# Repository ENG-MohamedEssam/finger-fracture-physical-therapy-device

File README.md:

# finger-fracture-physical-therapy-device

#### Note that this whole project was made by me from the Reverse-Engineering phase to the design to the fabrication of the final product

## **Abstract**

#### This project was for helping the physical therapist to help aid the patiets that had a broken or fractured finger
#### The device mainly uses a potentiometer to send the data of the the finger's angle to LCD and to the phone through a bluetooth module
#### The device has Arduino Nano as it's main controller, Potentiometer to send the Angle Data, LCD to show the data, Bluetooth module to send the data to the phone , 2 push buttons one for the hold of the readings, the second is for getting the angles in degree and minute format

#### The project went throgh four phases

## Phase 1 Idea
#### The idea was to replicate the behaviour of a digital protractor device that was already in the market to invent something that may help the patients with broken fingers
## Phase 2 Reverse-Engineering
#### So i started Reverse-Engineering the Digital protractor as shown below 

#### When i understood it's behaviour i started to find similar components in the Egyptian market 
#### the components that i didn't find was the induction encoder so i had to find a replacement
#### i thought of three things, Potentiometer, Normal Encoder, IMU
#### I even wrote codes for the three sesors.
## Problems 
#### IMU was too expensive for such a project but it kind of worked correctly
#### The encoders in Egypt had too little pulses so the error in Degrees was not acceptable
#### The potentiometer was the cheapest sensor so in mass production that was the ideal choice but it gave an error in the reading as well that was not acceptable and the Arduino Nano was only 10 bits in ADC

## Scenario to fix the Potentiameter's problem
#### To fix the problem in the potentiometer there were two solutions either i use the algorithm over sampling and decimation or i use the sliding window filter
#### so i went along with the over sampling and decimation technique, it was by having many readings in an array then get the average of it many times, that makes the reading more accurate.
#### The error after that algorithm was +/- 0.02 and that was more than acceptable.

## Phase 3 Design
#### In this phase i started to design the circuit on protues such as follows

#### After i made sure it works fine i turned to try the components connections on a bread board as follows 

#### Then i designed the circuit on Eagle-Cad program 
#### I even designed one of the three parts on SolidWorks as you can see below 

#### the other two parts were open source 

## Phase 4 fabrication
#### in this phase i fabricated the PCB and tested it and it worked fine, below are some images of the final product (The band)
.jpeg)

#### The following is a video of me explaining how the whole process works
[Explanation](https://drive.google.com/drive/folders/1u0ruocD8NN2b_IU45vWWJVkj_FHNx0_M?usp=share_link)

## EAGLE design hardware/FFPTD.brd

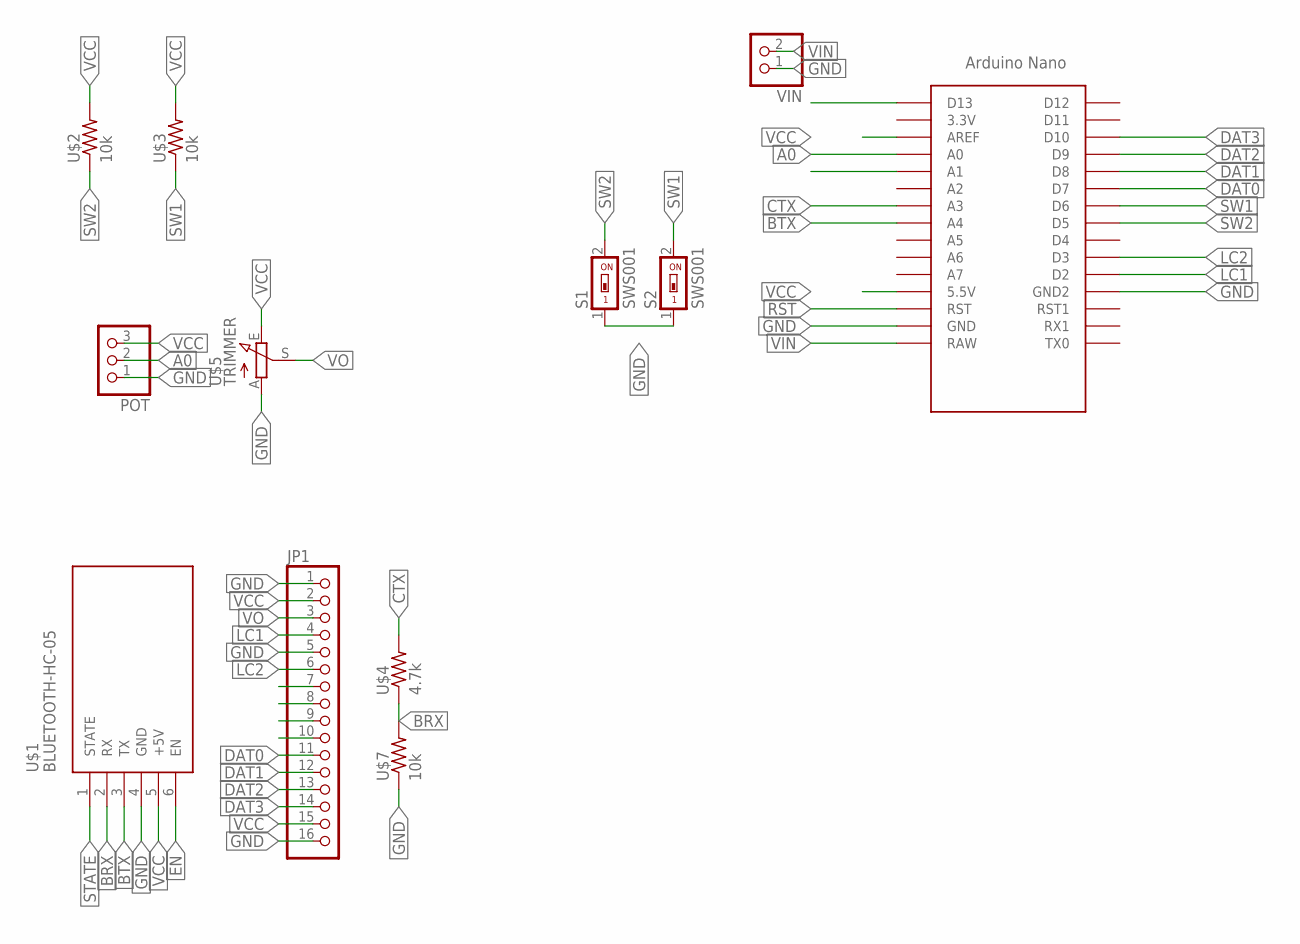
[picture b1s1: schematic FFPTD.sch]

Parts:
JP1: PINHD-1X16; 1X16
POT: PINHD-1X3; 1X03
S1, S2: SWS001; SMS-001
U$1: BLUETOOTH-HC-05; WIRELESS-BLUETOOTH-HC-05
U$2, U$3, U$7: 10k; 0204/7
U$4: 4.7k; 0204/7
U$5: TRIMMER; RJ9W
U$6: ARDUINO_NANO; NANO
VIN: PINHD-1X2; 1X02

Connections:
A0: POT.2, U$6.A0
BRX: U$1.2 (RX), U$4.1, U$7.2
BTX: U$1.3 (TX), U$6.A4
CTX: U$4.2, U$6.A3
DAT0: JP1.11, U$6.D7
DAT1: JP1.12, U$6.D8
DAT2: JP1.13, U$6.D9
DAT3: JP1.14, U$6.D10
EN: U$1.6 (EN)
GND: JP1.1, JP1.5, JP1.16, POT.1, S1.1, S2.1, U$1.4 (GND), U$5.A, U$6.GND, U$6.GND1 (GND2), U$7.1, VIN.1
LC1: JP1.4, U$6.D2
LC2: JP1.6, U$6.D3
RST: U$6.RST
STATE: U$1.1 (STATE)
SW1: S2.2, U$3.1, U$6.D6
SW2: S1.2, U$2.1, U$6.D5
VCC: JP1.2, JP1.15, POT.3, U$1.5 (+5V), U$2.2, U$3.2, U$5.E, U$6.5V (5.5V), U$6.AREF
VIN: U$6.RAW, VIN.2
VO: JP1.3, U$5.S

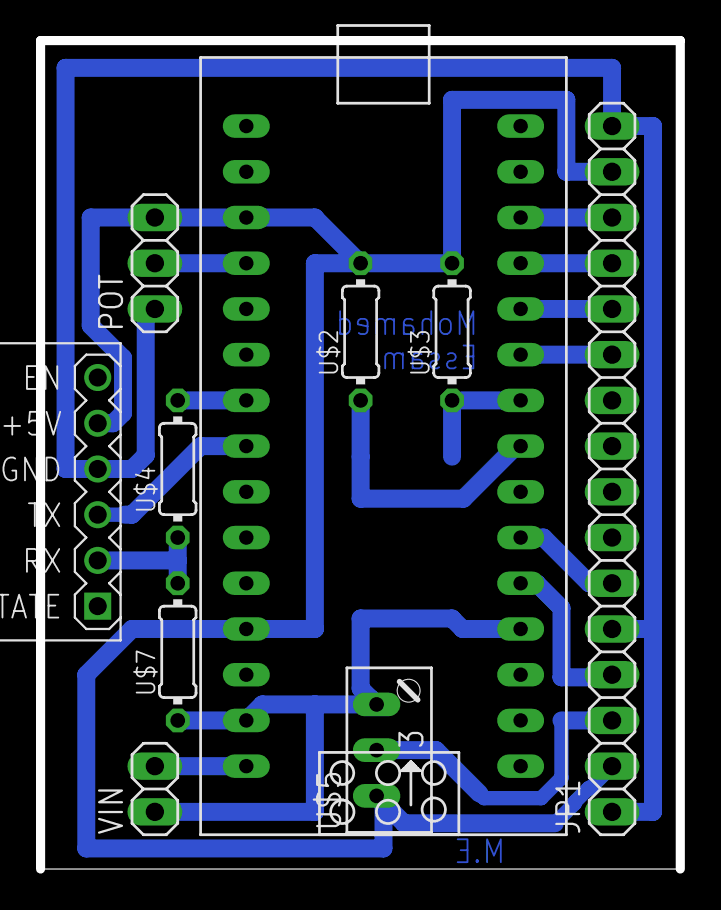
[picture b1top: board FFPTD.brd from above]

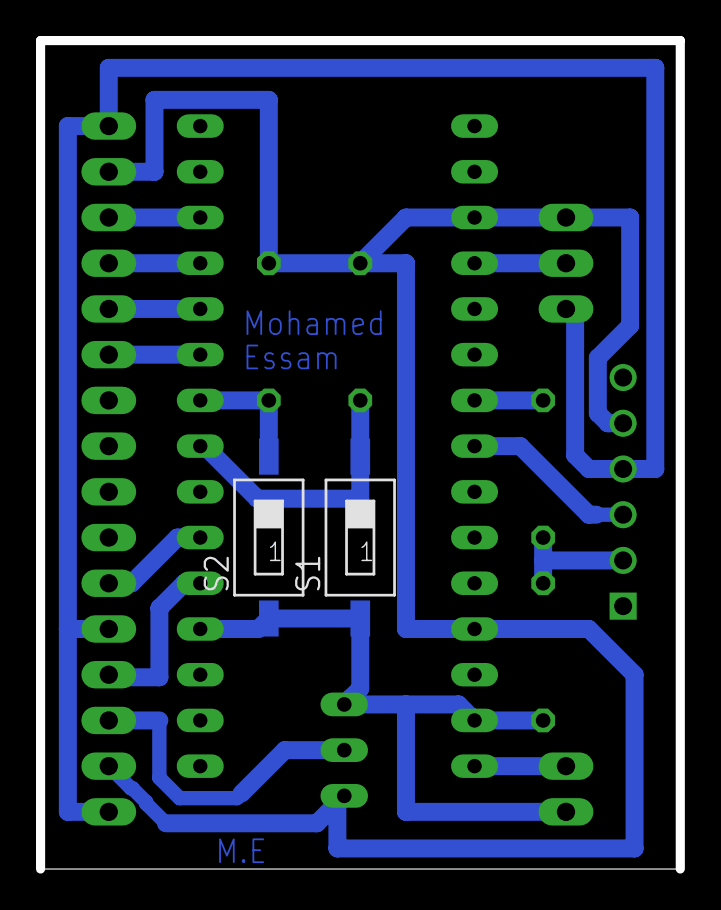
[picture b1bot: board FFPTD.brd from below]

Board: 2 copper layers, 35.5 x 46.0 mm, 12 parts (2 on the bottom side), 16 nets.

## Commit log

2022-12-05 Adding images and Explanation in readme file
2022-12-05 Edit in readme file
2022-12-05 Small edit in readme file
2022-12-07 Edit in readme
